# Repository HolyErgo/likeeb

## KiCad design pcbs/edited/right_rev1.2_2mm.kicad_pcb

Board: 2 copper layers, 16 parts (1 on the bottom side), 5 nets.

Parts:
S1, S2, S3, S4, S5, S6, S7, S8, S9, S10, S11, S12, S13, S14, S15: GateronLowProfileSwitch
_1: HKWClamshellSocket

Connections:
C6: S13.1, S14.1, S15.1, _1.5
C7: S10.1, S11.1, S12.1, _1.4
C8: S7.1, S8.1, S9.1, _1.3
C9: S4.1, S5.1, S6.1, _1.2
C10: S1.1, S2.1, S3.1, _1.1

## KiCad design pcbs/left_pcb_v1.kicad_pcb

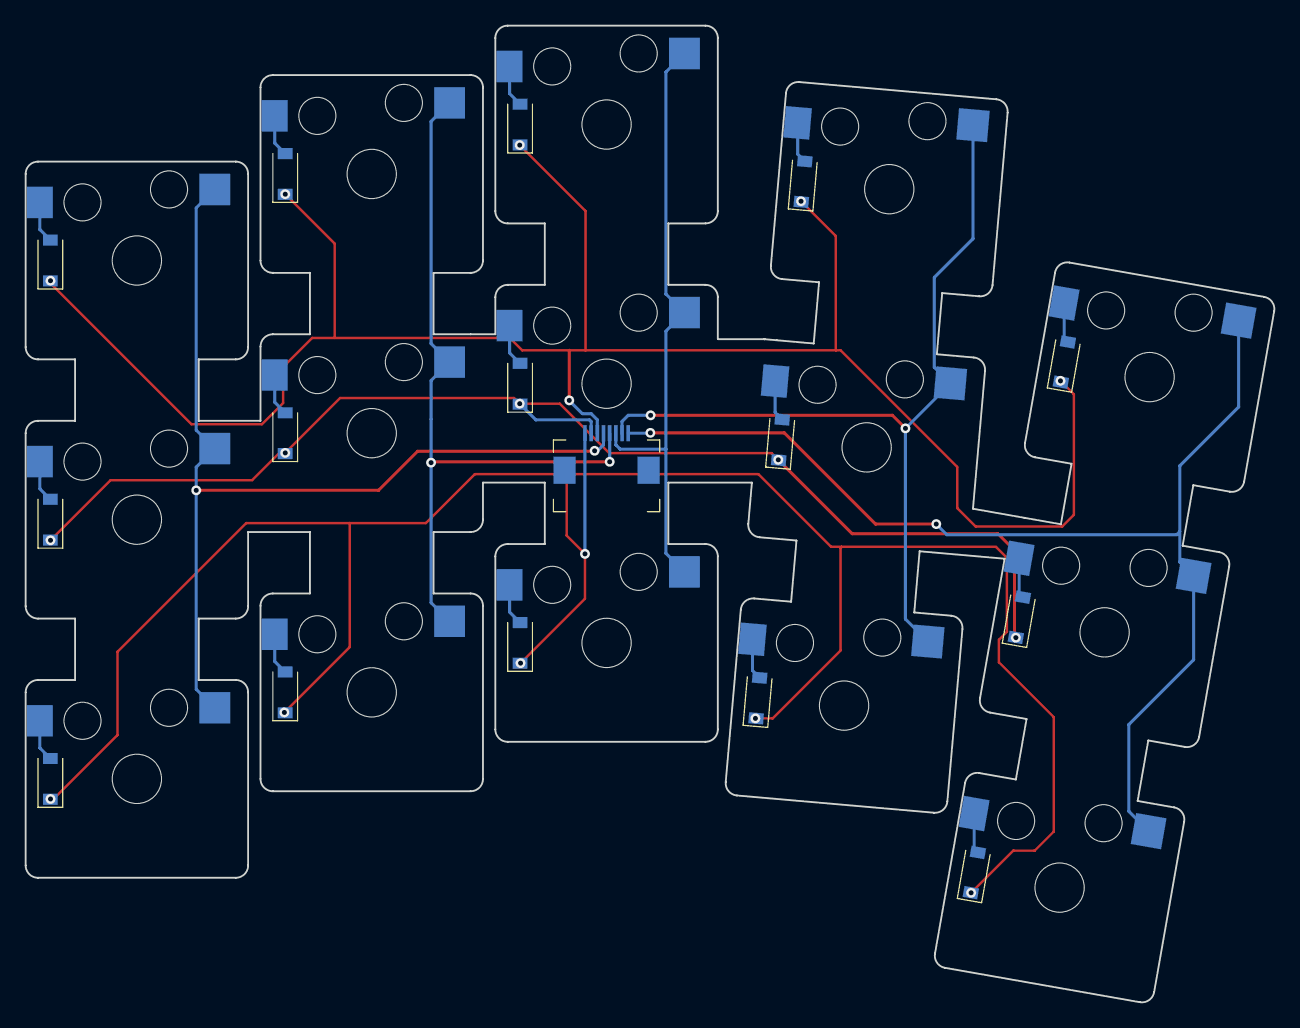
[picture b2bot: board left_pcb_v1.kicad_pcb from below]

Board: 2 copper layers, 101.0 x 79.0 mm, 31 parts (16 on the bottom side), 23 nets.

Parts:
D1, D2, D3, D4, D5, D6, D7, D8, D9, D10, D11, D12, D13, D14, D15: SmdDiode
S1, S2, S3, S4, S5, S6, S7, S8, S9, S10, S11, S12, S13, S14, S15: MX
_1: HKWClamshellSocket

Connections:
C1: S1.1, S2.1, S3.1, _1.8
C2: S4.1, S5.1, S6.1, _1.7
C3: S7.1, S8.1, S9.1, _1.6
C4: S10.1, S11.1, S12.1, _1.5
C5: S13.1, S14.1, S15.1, _1.4
R1: D2.1, D5.1, D8.1, D11.1, D14.1, _1.3
R2: D1.1, D4.1, D7.1, D10.1, D13.1, _1.2
R3: D3.1, D6.1, D9.1, D12.1, D15.1, _1.1
index_bottom: D12.2, S12.2
index_home: D10.2, S10.2
index_top: D11.2, S11.2
inner_bottom: D15.2, S15.2
inner_home: D13.2, S13.2
inner_top: D14.2, S14.2
middle_bottom: D9.2, S9.2
middle_home: D7.2, S7.2
middle_top: D8.2, S8.2
pinky_bottom: D3.2, S3.2
pinky_home: D1.2, S1.2
pinky_top: D2.2, S2.2
ring_bottom: D6.2, S6.2
ring_home: D4.2, S4.2
ring_top: D5.2, S5.2

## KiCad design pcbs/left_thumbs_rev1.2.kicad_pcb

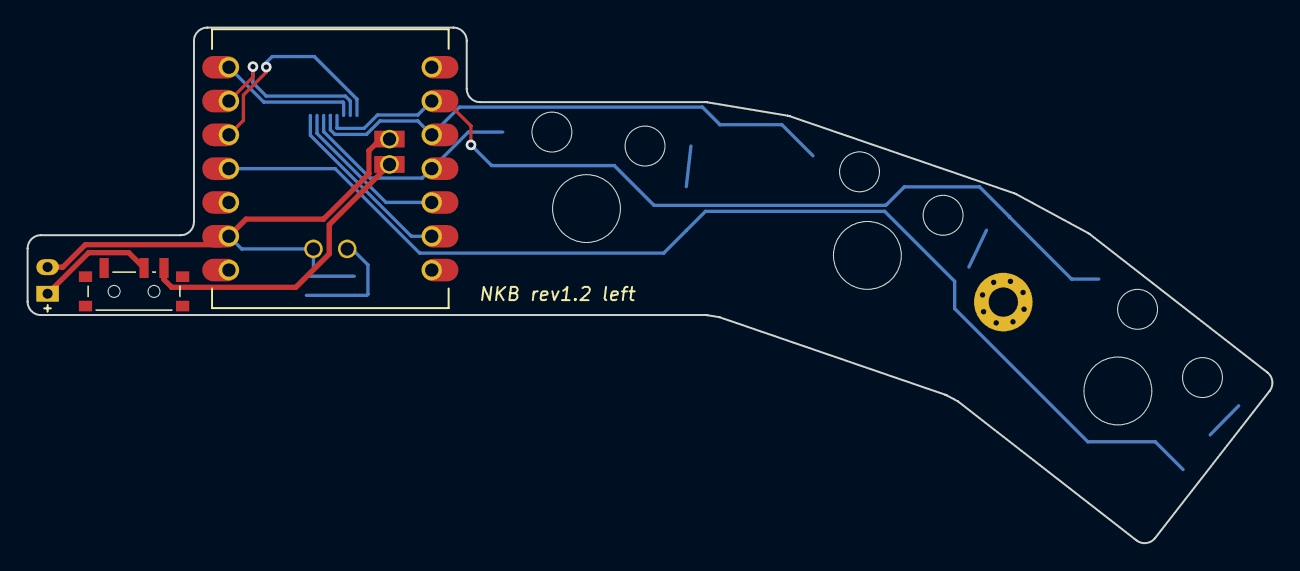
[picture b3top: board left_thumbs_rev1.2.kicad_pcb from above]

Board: 2 copper layers, 93.5 x 38.7 mm, 8 parts (1 on the bottom side), 5 nets.

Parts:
BAT1: BatteryPad
S1, S2, S3: GateronLowProfileSwitch
SW1: power_switch
SW2: sw_reset_side
_2: HKWClamshellSocket
_3: MountingHole_2.2mm_M2_Pad_Via

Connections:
BAT_P: BAT1.1, SW1.2
CT3: S1.1, _2.3
CT4: S2.1, _2.4
CT5: S3.1, _2.5
GND: BAT1.2, SW2.1

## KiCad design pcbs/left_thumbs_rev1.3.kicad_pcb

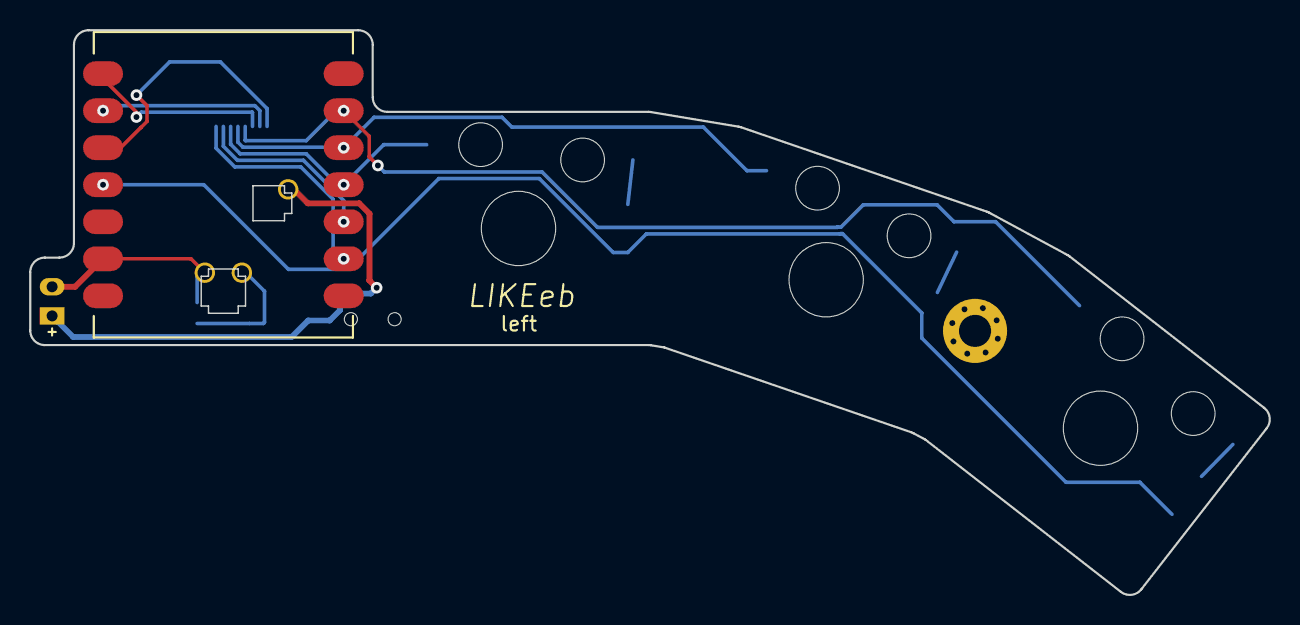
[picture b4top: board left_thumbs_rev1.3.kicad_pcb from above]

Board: 2 copper layers, 85.0 x 38.7 mm, 8 parts (1 on the bottom side), 9 nets.

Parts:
BAT1: BatteryPad
S1, S2, S3: GateronLowProfileSwitch
SW2: sw_reset_side
_1: Seeeduino XIAO nRF52840
_2: HKW FPC Socket
_3: MountingHole_2.2mm_M2_Pad_Via

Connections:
CT1: _1.2, _2.1
CT2: _1.3, _2.2
CT3: S1.1, _1.4, _2.3
CT4: S2.1, _1.5, _2.4
CT5: S3.1, _1.6, _2.5
GND: BAT1.2, SW2.1, _1.13
RLT1: _1.8, _2.6
RLT2: _1.9, _2.7
RLT3: _1.10, _2.8
